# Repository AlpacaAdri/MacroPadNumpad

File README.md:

# MacroPadNumpad
A custom Arduino based numpad made in Kicad.

This repo contains both the KICAD project files for the macropad PCB as well as the Arduino code needed to run it.
This project also uses the MX_Alpas_Hybrid library from https://github.com/ai03-2725/MX_Alps_Hybrid

this is very much a work in progress

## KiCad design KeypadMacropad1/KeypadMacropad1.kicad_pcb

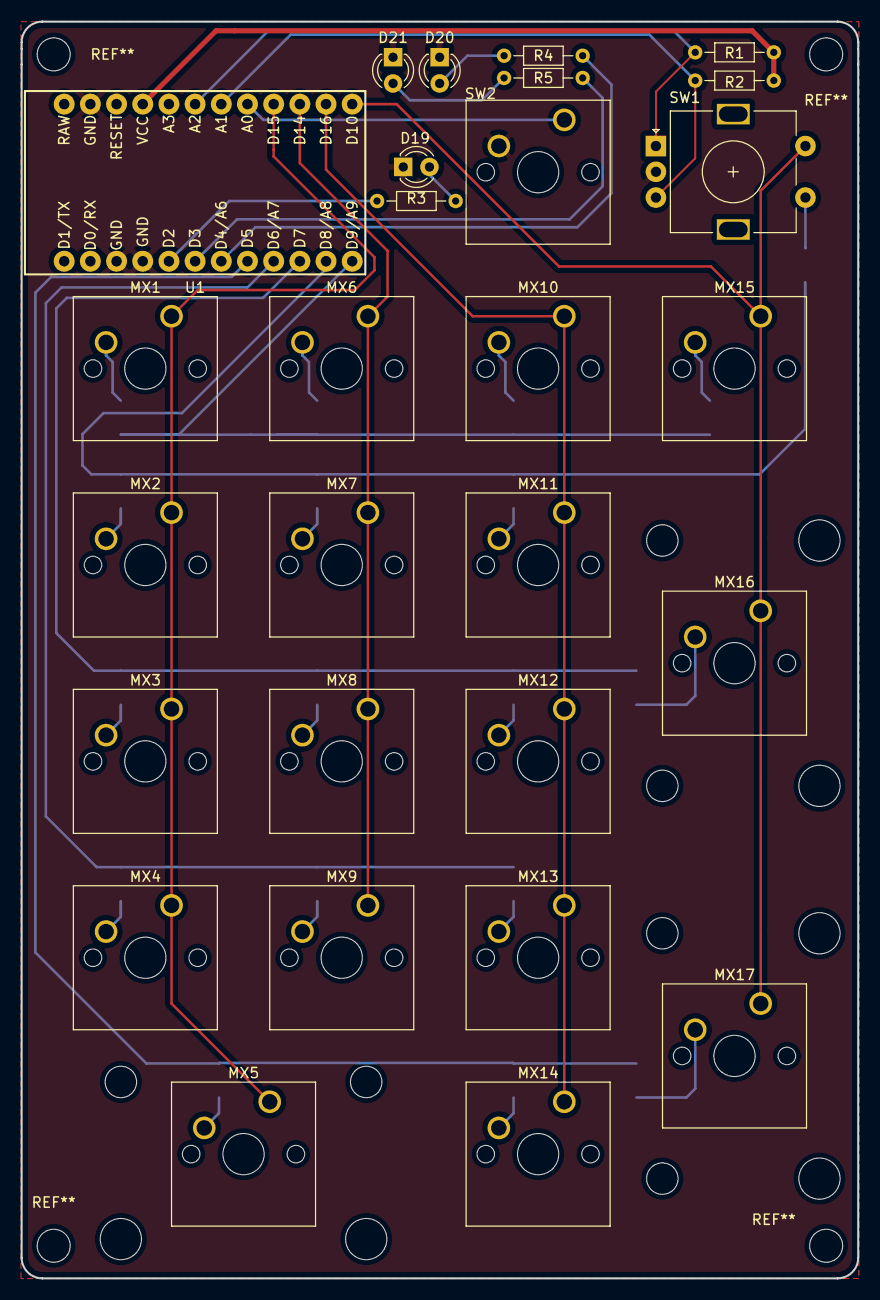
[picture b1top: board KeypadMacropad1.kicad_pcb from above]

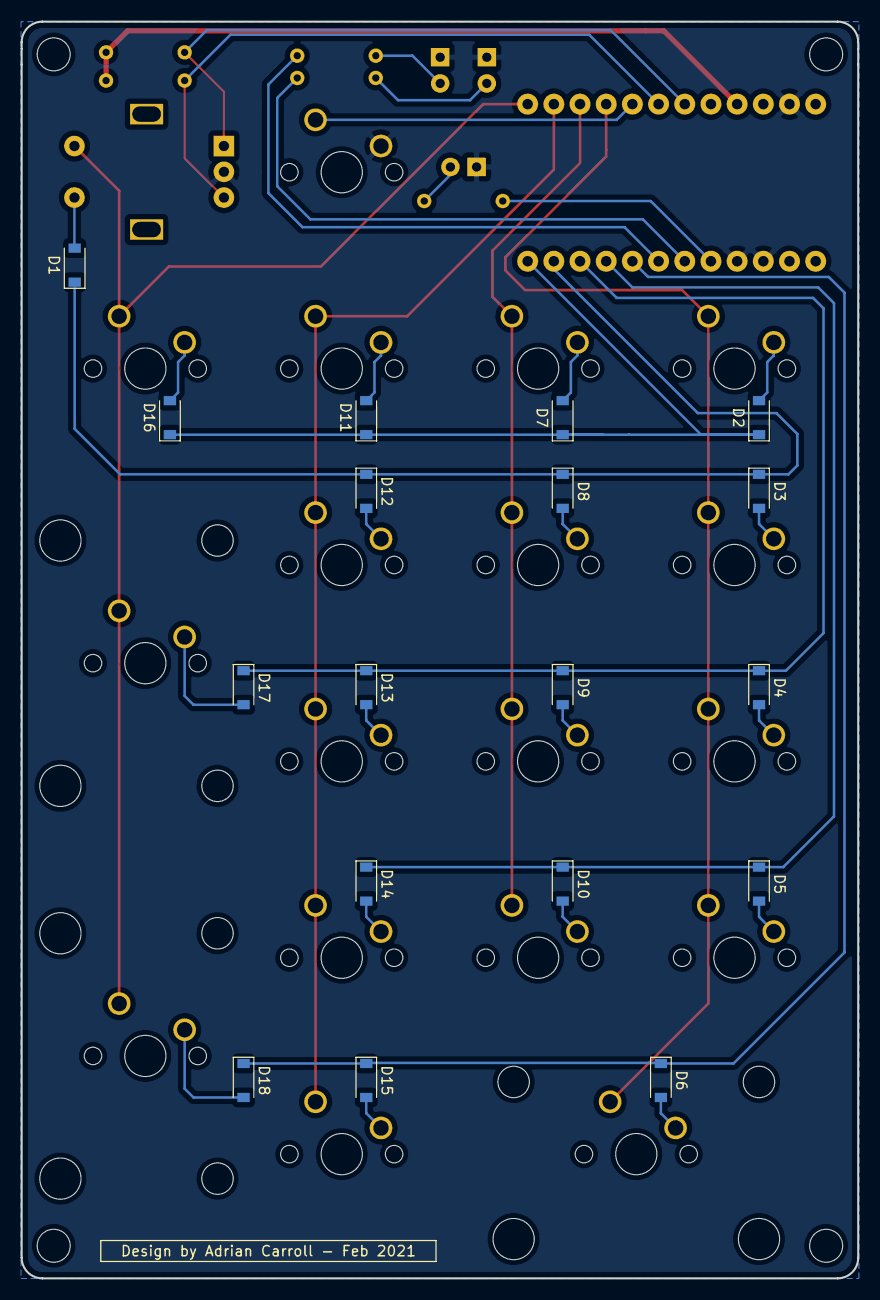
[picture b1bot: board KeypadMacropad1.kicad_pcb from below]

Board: 2 copper layers, 81.2 x 121.9 mm, 46 parts (18 on the bottom side), 38 nets.

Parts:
D1, D2, D3, D4, D5, D6, D7, D8, D9, D10, D11, D12, D13, D14, D15, D16, D17, D18: D; D_SOD-123
D19, D20, D21: LED; LED_D3.0mm
MX1: NUMLOK; SW_Cherry_MX_1.00u_PCB
MX2: SEVEN; SW_Cherry_MX_1.00u_PCB
MX3: FOUR; SW_Cherry_MX_1.00u_PCB
MX4: ONE; SW_Cherry_MX_1.00u_PCB
MX5: ZERO; SW_Cherry_MX_2.00u_PCB
MX6: FWDSLASH; SW_Cherry_MX_1.00u_PCB
MX7: EIGHT; SW_Cherry_MX_1.00u_PCB
MX8: FIVE; SW_Cherry_MX_1.00u_PCB
MX9: TWO; SW_Cherry_MX_1.00u_PCB
MX10: MULT; SW_Cherry_MX_1.00u_PCB
MX11: NINE; SW_Cherry_MX_1.00u_PCB
MX12: SIX; SW_Cherry_MX_1.00u_PCB
MX13: THREE; SW_Cherry_MX_1.00u_PCB
MX14: DECIMAL; SW_Cherry_MX_1.00u_PCB
MX15: MINUS; SW_Cherry_MX_1.00u_PCB
MX16: PLUS; SW_Cherry_MX_2.00u_Vertical_PCB
MX17: ENTER; SW_Cherry_MX_2.00u_Vertical_PCB
R1, R2: 1000 ohm; R_Axial_DIN0204_L3.6mm_D1.6mm_P7.62mm_Horizontal
R3, R4, R5: 220 ohm; R_Axial_DIN0204_L3.6mm_D1.6mm_P7.62mm_Horizontal
SW1: Rotary_Encoder_Switch; RotaryEncoder_Alps_EC11E-Switch_Vertical_H20mm
SW2: ModeChange; SW_Cherry_MX_1.00u_PCB
U1: Arduino_Pro_Micro

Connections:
+5V: R1.1, R2.1, U1.4
A1: R2.2, SW1.B, U1.7
A2: R1.2, SW1.A, U1.6
D4: R4.1, U1.19
GND: D19.1, D20.1, D21.1, SW1.C, SW2.2, U1.2, U1.15, U1.16
unnamed: D1.2, SW1.S1
unnamed: D2.2, MX1.2
unnamed: D3.2, MX2.2
unnamed: D4.2, MX3.2
unnamed: D5.2, MX4.2
unnamed: D6.2, MX5.2
unnamed: D7.2, MX6.2
unnamed: D8.2, MX7.2
unnamed: D9.2, MX8.2
unnamed: D10.2, MX9.2
unnamed: D11.2, MX10.2
unnamed: D12.2, MX11.2
unnamed: D13.2, MX12.2
unnamed: D14.2, MX13.2
unnamed: D15.2, MX14.2
unnamed: D16.2, MX15.2
unnamed: D17.2, MX16.2
unnamed: D18.2, MX17.2
unnamed: D19.2, R3.2
unnamed: D20.2, R4.2
unnamed: D21.2, R5.2
unnamed: SW2.1, U1.8
col1: MX1.1, MX2.1, MX3.1, MX4.1, MX5.1, U1.9
col2: MX6.1, MX7.1, MX8.1, MX9.1, U1.10
col3: MX10.1, MX11.1, MX12.1, MX13.1, MX14.1, U1.11
col4: MX15.1, MX16.1, MX17.1, SW1.S2, U1.12
d2: R3.1, U1.17
d3: R5.1, U1.18
row1: D2.1, D7.1, D11.1, D16.1, U1.24
row2: D1.1, D3.1, D8.1, D12.1, U1.23
row3: D4.1, D9.1, D13.1, D17.1, U1.22
row4: D5.1, D10.1, D14.1, U1.21
row5: D6.1, D15.1, D18.1, U1.20

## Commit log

2021-03-30 uploaded files
2021-03-30 rearranged files
2021-03-30 removed gerbers
2021-03-30 moved arduino footprint to internal library
2021-03-30 new file: PCB/#pcbTotal.dxf new file: PCB/Dxfs/KeypadMacropad1-B_Cu.dxf new file: PCB/Dxfs/KeypadMacropad1-B_Mask.dxf new file: PCB/Dxfs/KeypadMacropad1-B_Paste.dxf new file: PCB/Dxfs/KeypadMacropad1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
2021-03-30 deleted: KeypadMacropad1/#pcbTotal.dxf deleted: KeypadMacropad1/Dxfs/KeypadMacropad1-B_Cu.dxf deleted: KeypadMacropad1/Dxfs/KeypadMacropad1-B_Mask.dxf deleted: KeypadMacropad1/Dxfs/KeypadMacropad1-B_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
2021-03-31 modified: README.md
2021-04-02 added FreeCad model for front plate
2021-04-02 added 3d model of plate
2021-04-02 modified plate
2021-04-02 deleted: numPadPlate.obj
2021-04-02 remade numPadPlate
2021-04-04 reorganized Arduino code
2021-04-04 fixed issue with rows[] and cols[] not matching with hardware
2021-04-04 fixed issue #5 with long pressed keys
2021-04-05 added release function to each mode
2021-04-05 modified: macropadFirmware/sketch_feb25a/mode0.ino
2021-04-05 modified: macropadFirmware/sketch_feb25a/sketch_feb25a.ino
2021-04-05 made restructure branch
2021-04-06 removed unnecessary code from main function
2021-11-09 recommited
